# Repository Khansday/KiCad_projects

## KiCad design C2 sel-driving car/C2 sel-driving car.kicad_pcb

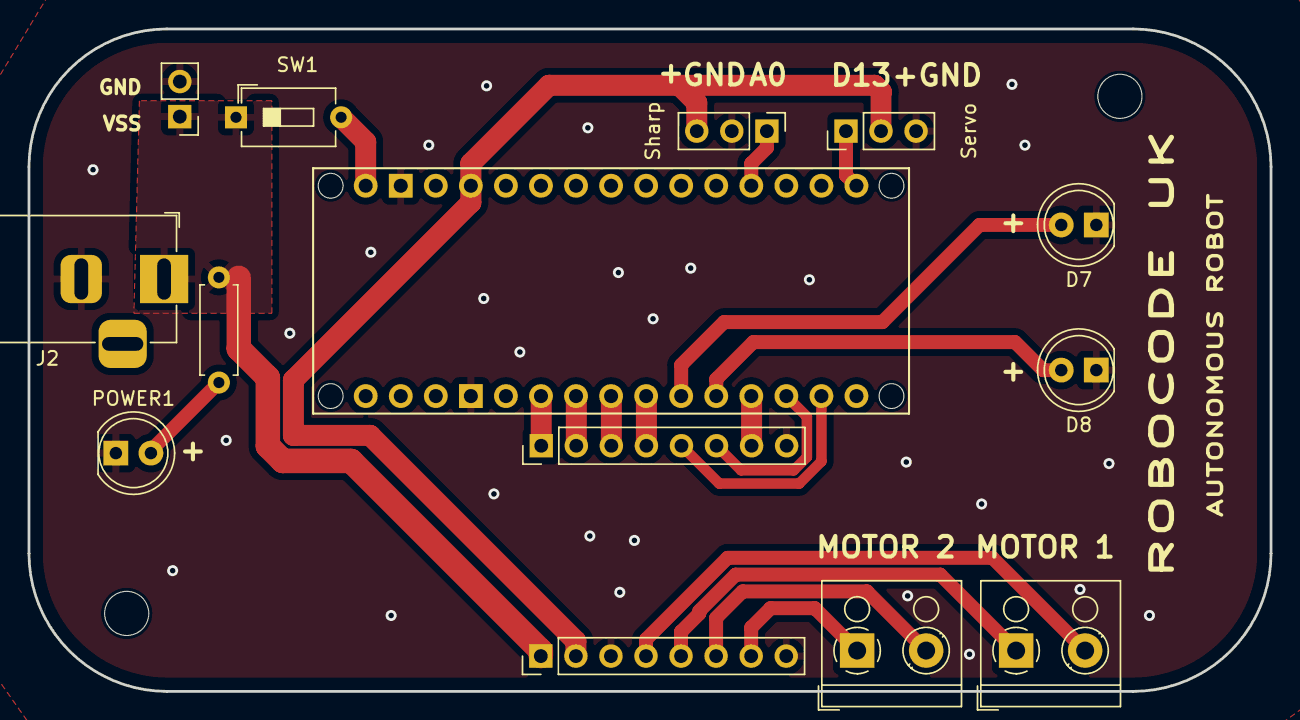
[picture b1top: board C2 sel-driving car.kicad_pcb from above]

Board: 2 copper layers, 90.0 x 48.0 mm, 14 parts (0 on the bottom side), 20 nets.

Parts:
D7, D8: LED; LED_D5.0mm
J1: Conn_01x02_Pin; PinHeader_1x02_P2.54mm_Vertical
J2: Barrel_Jack_MountingPin; BarrelJack_Horizontal
J4, J5: Conn_01x08_Socket; PinHeader_1x08_P2.54mm_Vertical
J6: Sharp; PinHeader_1x03_P2.54mm_Vertical
J7: Servo; PinHeader_1x03_P2.54mm_Vertical
MOTOR 1: Screw_Terminal_01x02; TerminalBlock_RND_205-00001_1x02_P5.00mm_Horizontal
MOTOR 2: MOTORB; TerminalBlock_RND_205-00001_1x02_P5.00mm_Horizontal
POWER1: LED; LED_D5.0mm
R1: 15K; R_Axial_DIN0207_L6.3mm_D2.5mm_P7.62mm_Horizontal
SW1: SW_DIP_x01; SW_DIP_SPSTx01_Slide_6.7x4.1mm_W7.62mm_P2.54mm_LowProfile
XA1: Arduino_Nano_Socket

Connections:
5V: J5.2, J6.3, J7.2, XA1.5V
A0: J6.1, XA1.A0
AIN1: J4.3, XA1.D5
AIN2: J4.2, XA1.D4
AO1: J5.4, MOTOR 1.2
AO2: J5.5, MOTOR 1.1
BIN1: J4.5, XA1.D11 (D11_MOSI)
BIN2: J4.6, XA1.D10
BO1: J5.6, MOTOR 2.2
BO2: J5.7, MOTOR 2.1
D13: J7.1, XA1.D13 (D13_SCK)
GND: D7.1 (K), D8.1 (K), J1.2, J2.2, J4.8, J5.3, J5.8, J6.2, J7.3, POWER1.1 (K), XA1.GND1 (GND), XA1.GND2 (GND)
LED1: D7.2 (A), XA1.D7
LED2: D8.2 (A), XA1.D8
unnamed: POWER1.2 (A), R1.2
unnamed: SW1.2, XA1.VIN
PWMA: J4.1, XA1.D3 (D3_INT1)
PWMB: J4.7, XA1.D9
STBY: J4.4, XA1.D6
Vss: J1.1, J2.1, J5.1, R1.1, SW1.1

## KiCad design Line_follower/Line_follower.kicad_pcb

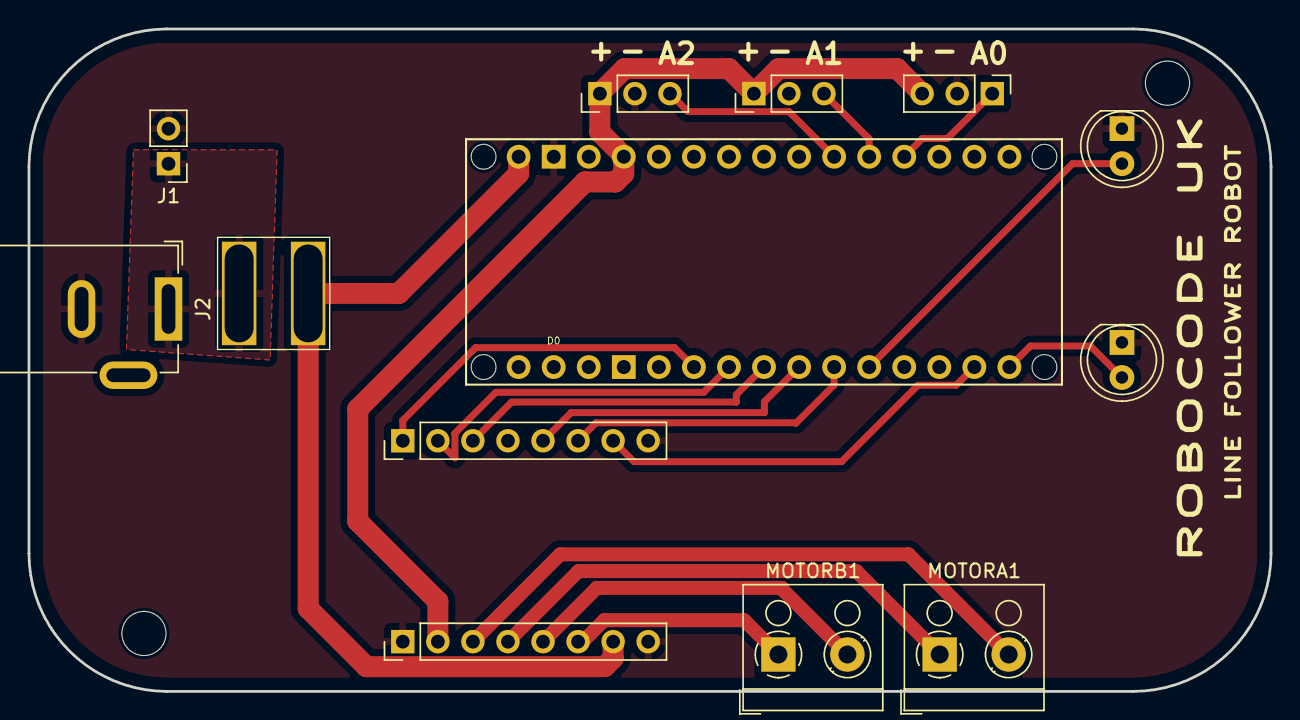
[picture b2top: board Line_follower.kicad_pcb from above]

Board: 2 copper layers, 90.0 x 48.0 mm, 13 parts (0 on the bottom side), 19 nets.

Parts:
D7, D8: LED; LED_D5.0mm
J1: Conn_01x02_Pin; PinHeader_1x02_P2.54mm_Vertical
J2: Barrel_Jack_MountingPin; BarrelJack_GCT_DCJ200-10-A_Horizontal
J3, J6, J7: Sharp; PinHeader_1x03_P2.54mm_Vertical
J4, J5: Conn_01x08_Socket; PinHeader_1x08_P2.54mm_Vertical
MOTORA1: Screw_Terminal_01x02; TerminalBlock_RND_205-00001_1x02_P5.00mm_Horizontal
MOTORB1: Screw_Terminal_01x02; TerminalBlock_RND_205-00001_1x02_P5.00mm_Horizontal
SW1: SW_DIP_x01; Rocker_Switch
XA1: Arduino_Nano_Socket

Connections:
5V: J3.1, J5.2, J6.3, J7.1, XA1.5V
A0: J6.1, XA1.A0
A1: J3.3, XA1.A1
A2: J7.3, XA1.A2
AIN1: J4.3, XA1.D5
AIN2: J4.2, XA1.D4
AO1: J5.3, MOTORA1.2
AO2: J5.4, MOTORA1.1
BIN1: J4.5, XA1.D6
BIN2: J4.6, XA1.D7
BO1: J5.5, MOTORB1.2
BO2: J5.6, MOTORB1.1
GND: D7.1 (K), D8.1 (K), J1.2, J2.2, J3.2, J4.8, J5.1, J5.8, J6.2, J7.2, XA1.GND1 (GND), XA1.GND2 (GND)
LED1: D7.2 (A), XA1.D8
LED2: D8.2 (A), XA1.D12 (D12_MISO)
PWMA: J4.1, XA1.D3 (D3_INT1)
PWMB: J4.7, XA1.D11 (D11_MOSI)
VIN: J5.7, SW1.2, XA1.VIN
Vss: J1.1, J2.1, SW1.1

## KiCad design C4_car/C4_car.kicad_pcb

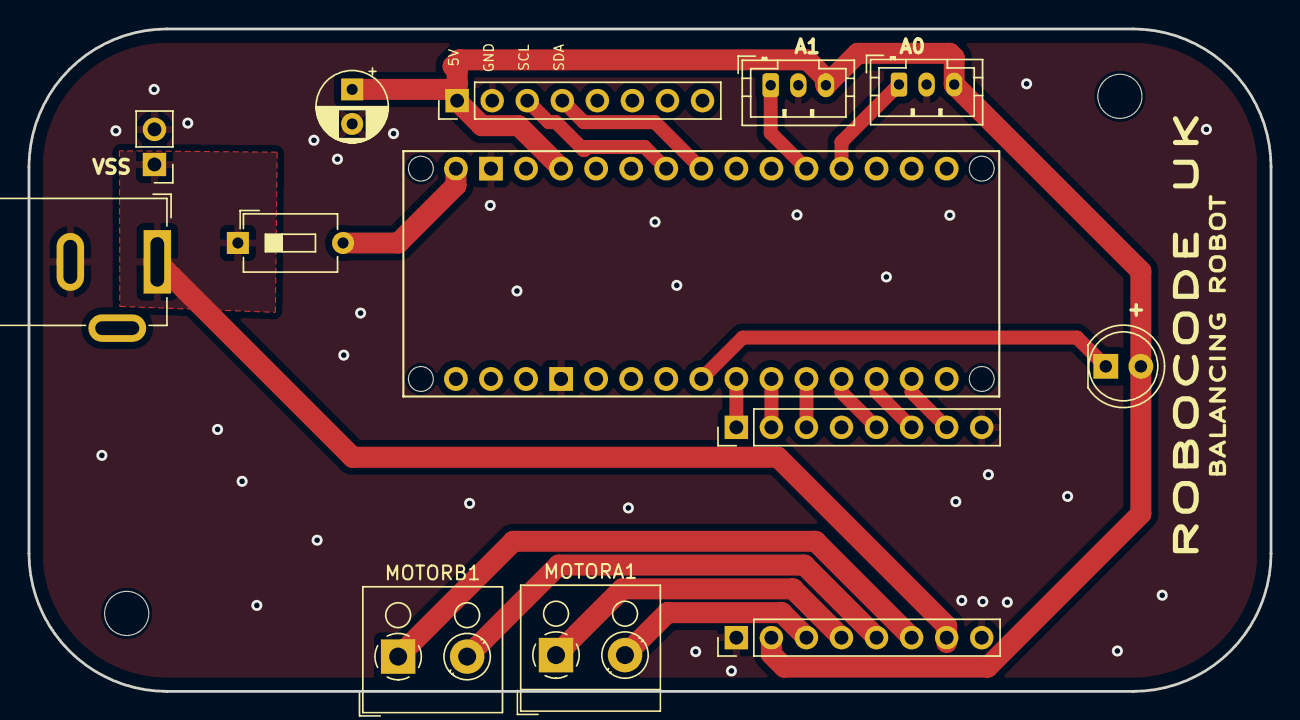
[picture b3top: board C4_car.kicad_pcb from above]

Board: 2 copper layers, 90.0 x 48.0 mm, 13 parts (0 on the bottom side), 19 nets.

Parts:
C1: C_Small; CP_Radial_D5.0mm_P2.50mm
D1: LED; LED_D5.0mm
J1: Conn_01x02_Pin; PinHeader_1x02_P2.54mm_Vertical
J2: Barrel_Jack_MountingPin; BarrelJack_GCT_DCJ200-10-A_Horizontal
J3, J4, J7: Conn_01x08_Socket; PinHeader_1x08_P2.54mm_Vertical
J5, J6: Sharp; JST_PH_B3B-PH-K_1x03_P2.00mm_Vertical
MOTORA1: Screw_Terminal_01x02; TerminalBlock_RND_205-00001_1x02_P5.00mm_Horizontal
MOTORB1: Screw_Terminal_01x02; TerminalBlock_RND_205-00001_1x02_P5.00mm_Horizontal
SW1: SW_DIP_x01; SW_DIP_SPSTx01_Slide_6.7x4.1mm_W7.62mm_P2.54mm_LowProfile
XA1: Arduino_Nano_Socket

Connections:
5V: C1.1, D1.2 (A), J4.2, J5.3, J6.3, J7.1, XA1.5V
A0: J5.1, XA1.A0
A1: J6.1, XA1.A1
AIN1: J3.3, XA1.D8
AIN2: J3.2, XA1.D7
AO1: J4.3, MOTORA1.2
AO2: J4.4, MOTORA1.1
BIN1: J3.6, XA1.D10
BIN2: J3.5, XA1.D9
BO1: J4.5, MOTORB1.2
BO2: J4.6, MOTORB1.1
GND: C1.2, J1.2, J2.2, J3.8, J4.1, J4.8, J5.2, J6.2, J7.2, XA1.GND1 (GND), XA1.GND2 (GND)
LED1: D1.1 (K), XA1.D5
unnamed: SW1.2, XA1.VIN
PWMA: J3.1, XA1.D6
PWMB: J3.7, XA1.D11 (D11_MOSI)
SCL: J7.3, XA1.A5 (A5/SCL)
SDA: J7.4, XA1.A4 (A4/SDA)
Vss: J1.1, J2.1, J4.7, SW1.1

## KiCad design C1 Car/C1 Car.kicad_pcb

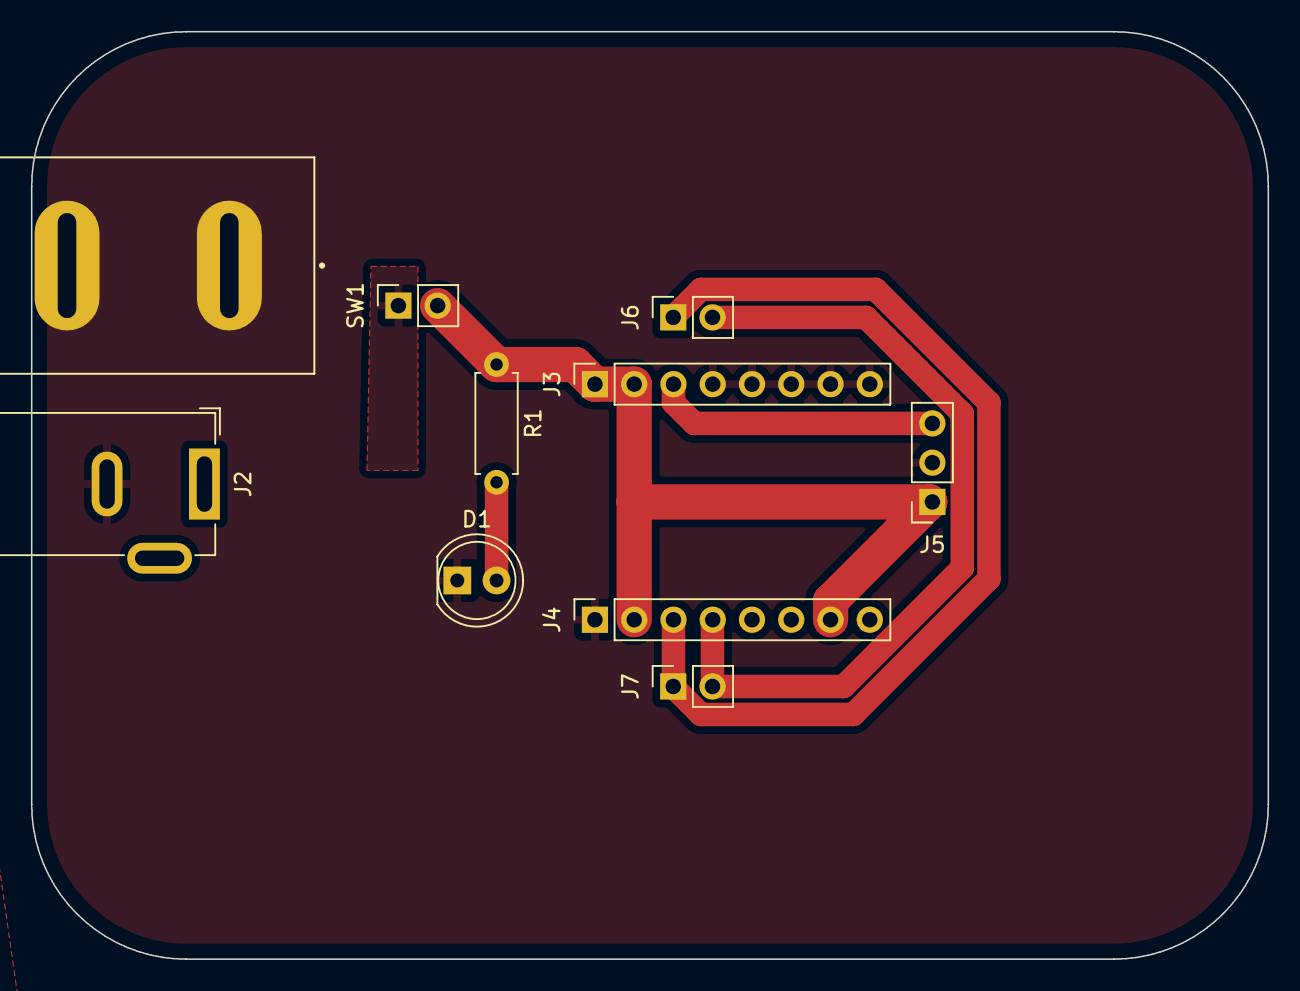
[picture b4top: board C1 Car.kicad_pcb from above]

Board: 2 copper layers, 80.0 x 60.0 mm, 9 parts (0 on the bottom side), 7 nets.

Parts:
D1: LED; LED_D5.0mm
J2: POWER PLUG; BarrelJack_GCT_DCJ200-10-A_Horizontal
J3, J4: MOTOR DRIVER; PinSocket_1x08_P2.54mm_Vertical
J5: IR SENSOR; PinSocket_1x03_P2.54mm_Vertical
J6: MOTOR 1; PinSocket_1x02_P2.54mm_Vertical
J7: MOTOR 2; PinSocket_1x02_P2.54mm_Vertical
R1: 15K; R_Axial_DIN0207_L6.3mm_D2.5mm_P7.62mm_Horizontal
SW1: POWER SWITCH; PinSocket_1x02_P2.54mm_Vertical

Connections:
/Vin: J2.1, SW1.1
A0: J3.3, J5.3
AIN2: J3.1, J3.2, J4.2, J4.7, J5.1, R1.1, SW1.2
AO1: J4.3, J6.1, J7.1
AO2: J4.4, J6.2, J7.2
GND: D1.1 (K), J2.2, J3.4, J3.5, J3.6, J3.7, J3.8, J4.1, J4.8, J5.2
unnamed: D1.2 (A), R1.2

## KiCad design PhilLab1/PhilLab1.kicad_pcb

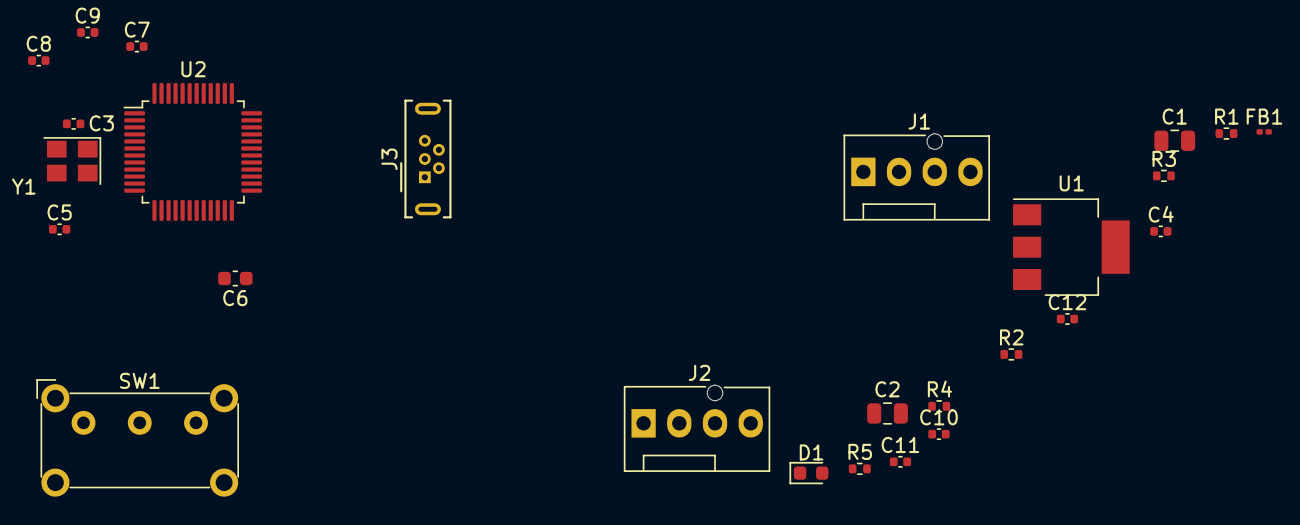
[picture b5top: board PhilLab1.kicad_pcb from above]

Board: 2 copper layers, 26 parts (0 on the bottom side), 16 nets, no tracks yet.

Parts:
C1, C2: 22u; C_0805_2012Metric
C3, C5: 10p; C_0402_1005Metric
C4, C7, C8, C9: 100n; C_0402_1005Metric
C6: 10u; C_0603_1608Metric
C10: 10n; C_0402_1005Metric
C11, C12: 1u; C_0402_1005Metric
D1: RED; LED_0603_1608Metric
FB1: 120R; L_0201_0603Metric
J1, J2: Conn_01x04_Male; FanPinHeader_1x04_P2.54mm_Vertical
J3: USB_B_Mini; USB_Micro-B_Wuerth_614105150721_Vertical
R1, R2, R3, R5: 1k5; R_0402_1005Metric
R4: 10k; R_0402_1005Metric
SW1: SW_SPDT; SW_E-Switch_EG1224_SPDT_Angled
U1: AMS1117-3.3; SOT-223-3_TabPin2
U2: STM32F103C8Tx; LQFP-48_7x7mm_P0.5mm
Y1: 16MHZ; Crystal_SMD_3225-4Pin_3.2x2.5mm

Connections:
+3.3V: C2.1, C6.1, C7.1, C8.1, C9.1, C12.1, D1.2 (A), FB1.2, J1.1, J2.1, R2.1, R3.1, R5.1, SW1.3 (C), U1.2 (VO), U2.1 (VBAT), U2.24 (VDD), U2.36 (VDD), U2.48 (VDD)
+3.3VA: C10.1, C11.1, FB1.1, U2.9 (VDDA)
/HSE_IN: C5.1, U2.6 (PD1), Y1.3
/HSE_OUT: C3.1, U2.5 (PD0), Y1.1
/I2C_CLK: J1.2, R2.2, U2.21 (PB10)
/I2C_DATA: J1.3, R3.2, U2.22 (PB11)
/NRESET: C4.1, U2.7 (NRST)
/PW_LED_K: D1.1 (K), R1.1
/SWBOOT: R4.1, SW1.2 (B)
/SW_CLK: J2.3, U2.37 (PA14)
/SW_DIO: J2.2, U2.34 (PA13)
/USB_D+: J3.3 (D+), R5.2, U2.33 (PA12)
/USB_D-: J3.2 (D-), U2.32 (PA11)
GND: C1.2, C2.2, C3.2, C4.2, C5.2, C6.2, C7.2, C8.2, C9.2, C10.2, C11.2, C12.2, J1.4, J2.4, J3.5 (GND), R1.2, SW1.1 (A), U1.1 (GND), U2.8 (VSSA), U2.23 (VSS), U2.35 (VSS), U2.47 (VSS), Y1.2, Y1.4
unnamed: R4.2, U2.44 (BOOT0)
VBUS: C1.1, J3.1 (VBUS), U1.3 (VI)

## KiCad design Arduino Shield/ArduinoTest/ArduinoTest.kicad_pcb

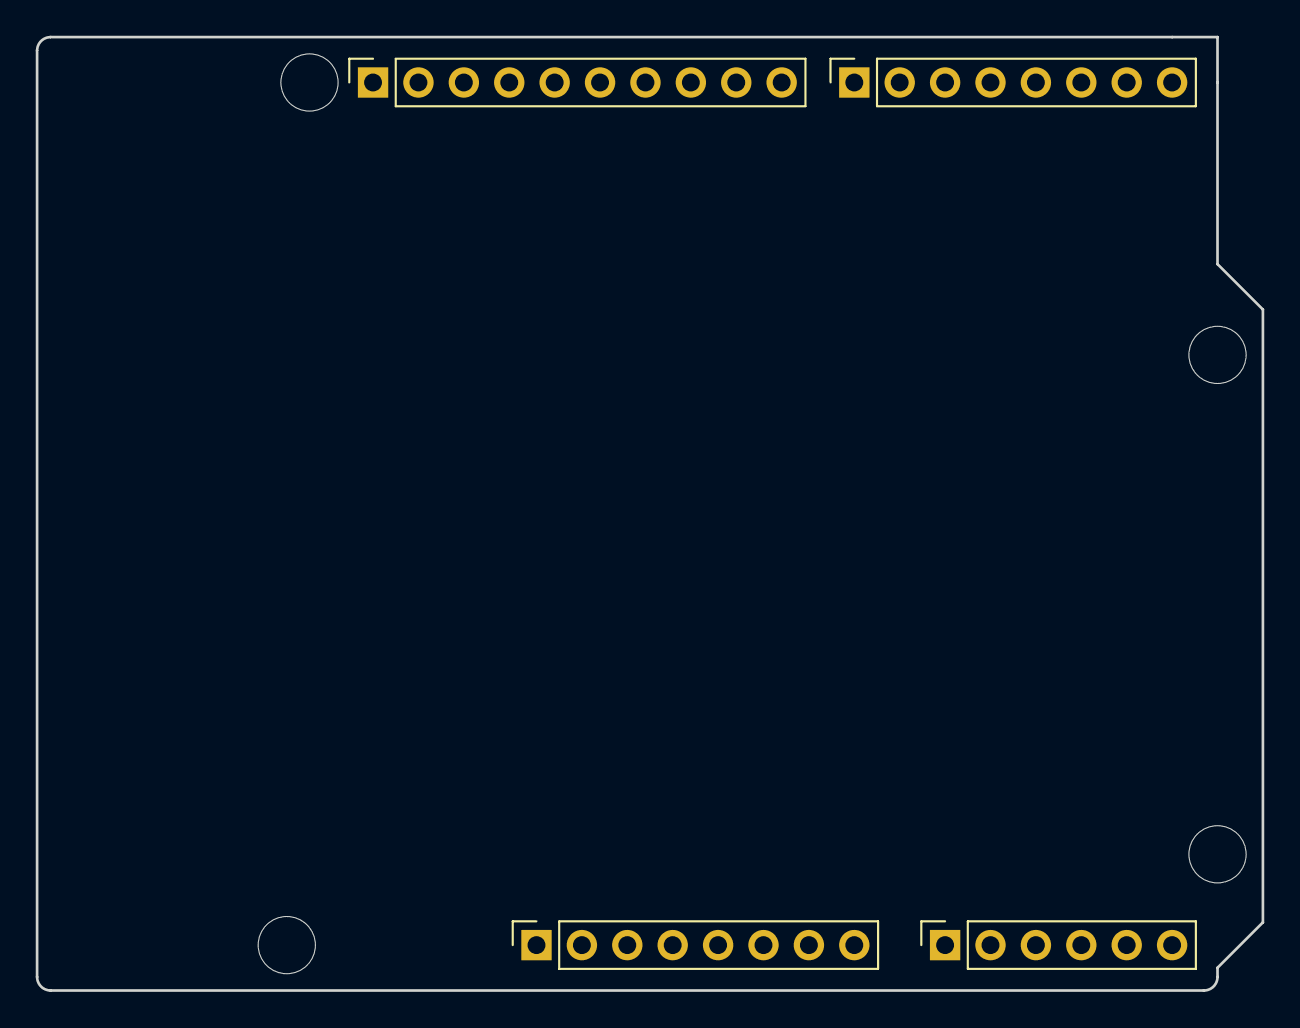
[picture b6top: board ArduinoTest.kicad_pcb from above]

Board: 2 copper layers, 68.6 x 53.3 mm, 8 parts (0 on the bottom side), 3 nets, no tracks yet.

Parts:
J1: Power; PinSocket_1x08_P2.54mm_Vertical
J2: Digital/PWM; PinSocket_1x10_P2.54mm_Vertical
J3: Analog; PinSocket_1x06_P2.54mm_Vertical
J4: Digital/PWM; PinSocket_1x08_P2.54mm_Vertical
MH1, MH2, MH3, MH4: MountingHole_3.2mm

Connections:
/SCL/A5: J2.1, J3.6
/SDA/A4: J2.2, J3.5
GND: J1.6, J1.7, J2.4

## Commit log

2023-09-18 KiCad project
2024-12-30 updated dec 30
